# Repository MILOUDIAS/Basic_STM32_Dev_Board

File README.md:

# Basic_STM32_Dev_Board

## Description

The Project is about an STM32 based development board used mainly for educative purposes and prototyping designed in Kicad 8

### PCB

### Sshematic

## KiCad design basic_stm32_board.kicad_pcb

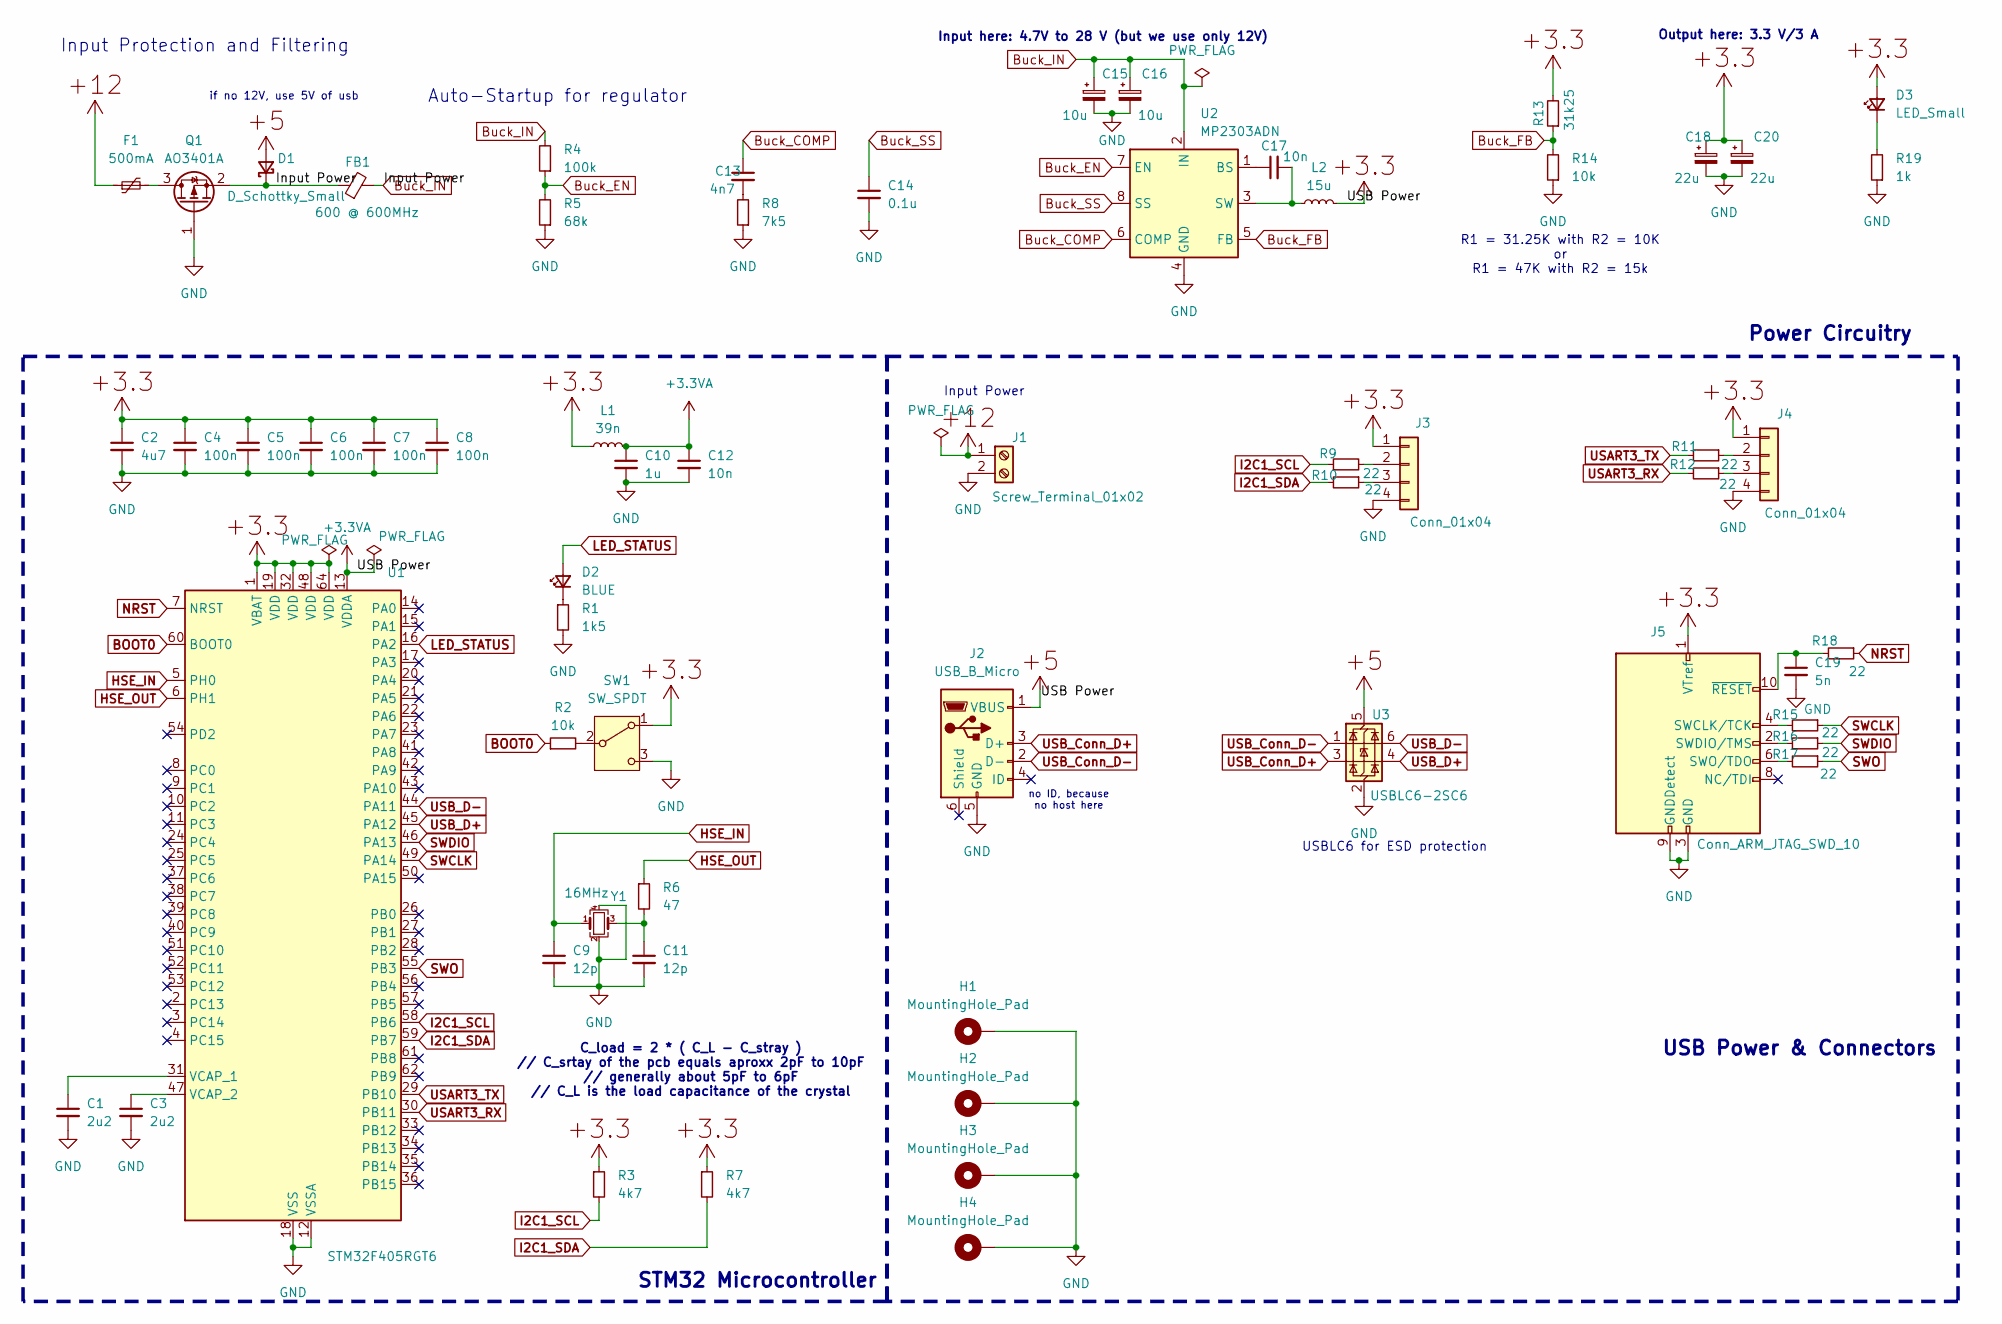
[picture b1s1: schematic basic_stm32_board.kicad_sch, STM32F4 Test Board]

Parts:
C1, C3: 2u2; C_1206_3216Metric_Pad1.33x1.80mm_HandSolder
C2: 4u7; C_1206_3216Metric_Pad1.33x1.80mm_HandSolder
C4, C5, C6, C7, C8: 100n; C_0201_0603Metric_Pad0.64x0.40mm_HandSolder
C9, C11: 12p; C_0201_0603Metric_Pad0.64x0.40mm_HandSolder
C10: 1u; C_1206_3216Metric_Pad1.33x1.80mm_HandSolder
C12, C17: 10n; C_0201_0603Metric_Pad0.64x0.40mm_HandSolder
C13: 4n7; C_0201_0603Metric_Pad0.64x0.40mm_HandSolder
C14: 0.1u; C_0201_0603Metric_Pad0.64x0.40mm_HandSolder
C15, C16: 10u; C_1206_3216Metric_Pad1.33x1.80mm_HandSolder
C18, C20: 22u; C_1206_3216Metric_Pad1.33x1.80mm_HandSolder
C19: 5n; C_0201_0603Metric_Pad0.64x0.40mm_HandSolder
D1: D_Schottky_Small; D_0603_1608Metric_Pad1.05x0.95mm_HandSolder
D2: BLUE; LED_0603_1608Metric_Pad1.05x0.95mm_HandSolder
D3: LED_Small; LED_0603_1608Metric_Pad1.05x0.95mm_HandSolder
F1: 500mA; Fuse_1206_3216Metric_Pad1.42x1.75mm_HandSolder
FB1: 600 @ 600MHz; L_1206_3216Metric_Pad1.22x1.90mm_HandSolder
H1, H2, H3, H4: MountingHole_Pad; MountingHole_2.2mm_M2_ISO7380_Pad
J1: Screw_Terminal_01x02; TerminalBlock_Phoenix_PT-1,5-2-3.5-H_1x02_P3.50mm_Horizontal
J2: USB_B_Micro; USB_Micro-AB_Molex_47590-0001
J3, J4: Conn_01x04; FanPinHeader_1x04_P2.54mm_Vertical
J5: Conn_ARM_JTAG_SWD_10; PinHeader_2x05_P1.27mm_Vertical
L1: 39n; L_0603_1608Metric_Pad1.05x0.95mm_HandSolder
L2: 15u; L_6.3x6.3_H3
Q1: AO3401A; SOT-23
R1: 1k5; R_0603_1608Metric_Pad0.98x0.95mm_HandSolder
R2, R14: 10k; R_0603_1608Metric_Pad0.98x0.95mm_HandSolder
R3, R7: 4k7; R_0603_1608Metric_Pad0.98x0.95mm_HandSolder
R4: 100k; R_0603_1608Metric_Pad0.98x0.95mm_HandSolder
R5: 68k; R_0603_1608Metric_Pad0.98x0.95mm_HandSolder
R6: 47; R_0402_1005Metric_Pad0.72x0.64mm_HandSolder
R8: 7k5; R_0603_1608Metric_Pad0.98x0.95mm_HandSolder
R9, R10, R11, R12, R15, R16, R17, R18: 22; R_0402_1005Metric_Pad0.72x0.64mm_HandSolder
R13: 31k25; R_0603_1608Metric_Pad0.98x0.95mm_HandSolder
R19: 1k; R_0603_1608Metric_Pad0.98x0.95mm_HandSolder
SW1: SW_SPDT; SW_SPDT_PCM12
U1: STM32F405RGT6; LQFP-64_10x10mm_P0.5mm
U2: MP2303ADN; SOIC-8-1EP_3.9x4.9mm_P1.27mm_EP2.62x3.51mm
U3: USBLC6-2SC6; SOT-23-6
Y1: 16MHz; Crystal_SMD_0603-4Pin_6.0x3.5mm

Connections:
+3.3VA: C2.1, C4.1, C5.1, C6.1, C7.1, C8.1, C10.1, C12.1, C18.1, C20.1, D1.2 (A), D3.2 (A), J2.1 (VBUS), J3.1, J4.1, J5.1 (VTref), L1.1, L1.2, L2.2, R3.1, R7.1, R13.2, SW1.1 (A), U1.1 (VBAT), U1.13 (VDDA), U1.19 (VDD), U1.32 (VDD), U1.48 (VDD), U1.64 (VDD), U3.5 (VBUS)
BOOT0: R2.1, U1.60 (BOOT0)
Buck_COMP: C13.1, U2.6 (COMP)
Buck_EN: R4.1, R5.2, U2.7 (EN)
Buck_FB: R13.1, R14.2, U2.5 (FB)
Buck_IN: C15.1, C16.1, D1.1 (K), FB1.1, FB1.2, Q1.2 (S), R4.2, U2.2 (IN)
Buck_SS: C14.1, U2.8 (SS)
GND: C1.2, C2.2, C3.2, C4.2, C5.2, C6.2, C7.2, C8.2, C9.2, C10.2, C11.2, C12.2, C14.2, C15.2, C16.2, C18.2, C19.2, C20.2, H1.1, H2.1, H3.1, H4.1, J1.2, J2.5 (GND), J3.4, J4.4, J5.3 (GND), J5.5 (GND), J5.9 (GNDDetect), Q1.1 (G), R1.2, R5.1, R8.1, R14.1, R19.1, SW1.3 (C), U1.12 (VSSA), U1.18 (VSS), U1.63 (VSS), U2.4 (GND), U3.2 (GND), Y1.2, Y1.4
HSE_IN: C9.1, U1.5 (PH0), Y1.1
HSE_OUT: R6.1, U1.6 (PH1)
I2C1_SCL: R3.2, R9.1, U1.58 (PB6)
I2C1_SDA: R7.2, R10.2, U1.59 (PB7)
LED_STATUS: D2.2 (A), U1.16 (PA2)
NRST: R18.1, U1.7 (NRST)
unnamed: C11.1, R6.2, Y1.3
unnamed: C13.2, R8.2
unnamed: D2.1 (K), R1.1
unnamed: D3.1 (K), R19.2
unnamed: J3.2, R9.2
unnamed: J3.3, R10.1
unnamed: J4.2, R11.1
unnamed: J4.3, R12.1
unnamed: J5.4 (SWCLK/TCK), R15.2
unnamed: J5.2 (SWDIO/TMS), R16.2
unnamed: J5.6 (SWO/TDO), R17.2
unnamed: C19.1, J5.10 (~RESET), R18.2
unnamed: F1.2, Q1.3 (D)
unnamed: R2.2, SW1.2 (B)
unnamed: C1.1, U1.31 (VCAP_1)
unnamed: C3.1, U1.47 (VCAP_2)
unnamed: C17.1, U2.1 (BS)
unnamed: C17.2, L2.1, U2.3 (SW)
P,+12: F1.1, J1.1
SWCLK: R15.1, U1.49 (PA14)
SWDIO: R16.1, U1.46 (PA13)
SWO: R17.1, U1.55 (PB3)
USART3_RX: R12.2, U1.30 (PB11)
USART3_TX: R11.2, U1.29 (PB10)
USB_Conn_D+: J2.3 (D+), U3.3 (I/O2)
USB_Conn_D-: J2.2 (D-), U3.1 (I/O1)
USB_D+: U1.45 (PA12), U3.4 (I/O2)
USB_D-: U1.44 (PA11), U3.6 (I/O1)

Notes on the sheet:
Input here: 4.7V to 28 V (but we use only 12V)
Power Circuitry
Input Protection and Filtering
USB Power & Connectors
if no 12V, use 5V of usb
Output here: 3.3 V/3 A
STM32 Microcontroller
R1 = 31.25K with R2 = 10K or R1 = 47K with R2 = 15k
C_load = 2 * ( C_L - C_stray ) // C_srtay of the pcb equals aproxx 2pF to 10pF // generally about 5pF to 6pF // C_L is the load capacitance of the crystal
no ID, because no host here
USBLC6 for ESD protection
Input Power
Auto-Startup for regulator

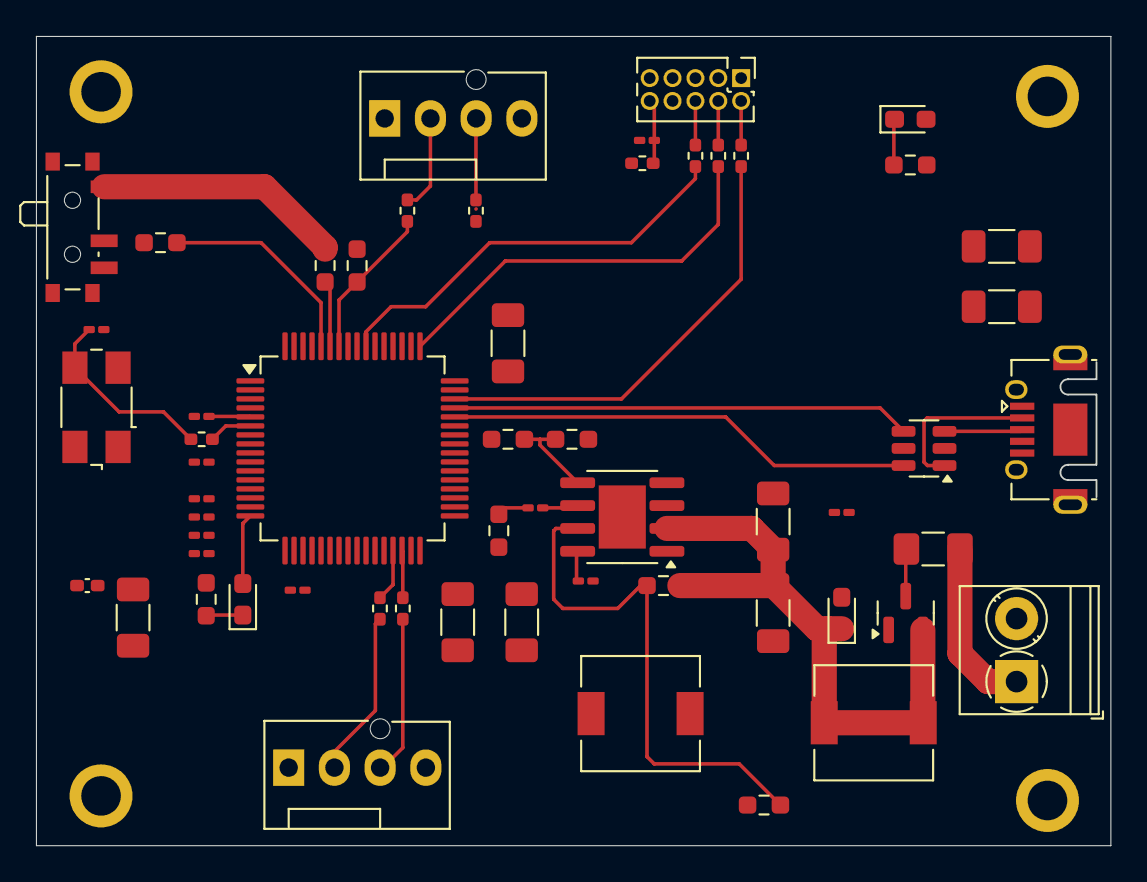
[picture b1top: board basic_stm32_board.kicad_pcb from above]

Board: 4 copper layers, 59.6 x 44.9 mm, 61 parts (0 on the bottom side), 42 nets.

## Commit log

2024-05-01 Project init
2024-05-01 removed all DRC errors
2024-05-01 some layout adjustement
2024-05-07 Working now on signal traces..
2024-05-08 experimenting with tarces placement..
2024-05-09 added missing 3d models
2024-05-09 changed some footprints
2024-06-04 Removed all traces
2024-06-04 Footprint placement changed
2024-06-10 added signal traces
2024-06-10 Added some demo images
2024-06-10 typo fixed
